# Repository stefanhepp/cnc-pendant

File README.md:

README
------

CNC Pendant for bCNC grbl controller.

License
-------
Shield: [![CC BY-SA 4.0][cc-by-sa-shield]][cc-by-sa]

This work is licensed under a
[Creative Commons Attribution-ShareAlike 4.0 International License][cc-by-sa].

[![CC BY-SA 4.0][cc-by-sa-image]][cc-by-sa]

[cc-by-sa]: http://creativecommons.org/licenses/by-sa/4.0/
[cc-by-sa-image]: https://licensebuttons.net/l/by-sa/4.0/88x31.png
[cc-by-sa-shield]: https://img.shields.io/badge/License-CC%20BY--SA%204.0-lightgrey.svg

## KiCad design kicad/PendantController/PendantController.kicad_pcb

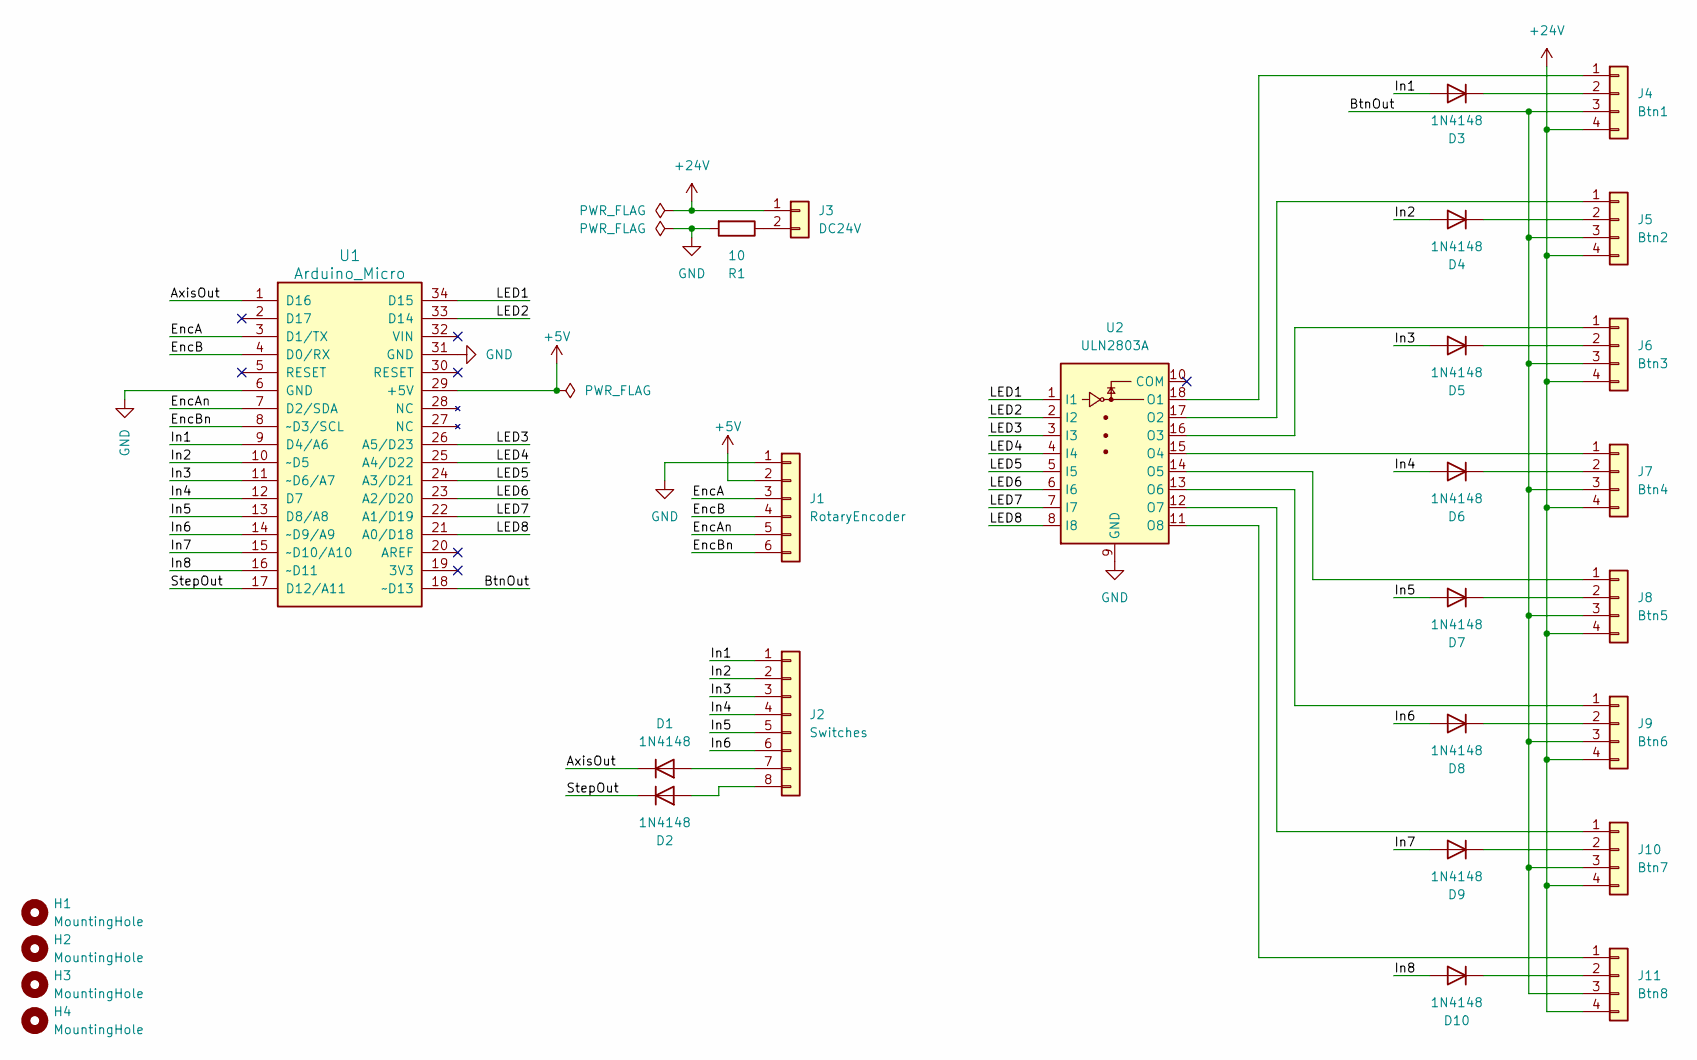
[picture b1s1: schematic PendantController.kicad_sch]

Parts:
D1, D2, D3, D4, D5, D6, D7, D8, D9, D10: 1N4148; D_DO-35_SOD27_P7.62mm_Horizontal
H1, H2, H3, H4: MountingHole; MountingHole_3.2mm_M3
J1: RotaryEncoder; PinHeader_1x06_P2.54mm_Vertical
J2: Switches; PinHeader_1x08_P2.54mm_Vertical
J3: DC24V; PinHeader_1x02_P2.54mm_Vertical
J4: Btn1; JST_XH_B4B-XH-A_1x04_P2.50mm_Vertical
J5: Btn2; JST_XH_B4B-XH-A_1x04_P2.50mm_Vertical
J6: Btn3; JST_XH_B4B-XH-A_1x04_P2.50mm_Vertical
J7: Btn4; JST_XH_B4B-XH-A_1x04_P2.50mm_Vertical
J8: Btn5; JST_XH_B4B-XH-A_1x04_P2.50mm_Vertical
J9: Btn6; JST_XH_B4B-XH-A_1x04_P2.50mm_Vertical
J10: Btn7; JST_XH_B4B-XH-A_1x04_P2.50mm_Vertical
J11: Btn8; JST_XH_B4B-XH-A_1x04_P2.50mm_Vertical
R1: 10; R_Axial_DIN0309_L9.0mm_D3.2mm_P12.70mm_Horizontal
U1: Arduino_Micro
U2: ULN2803A; DIP-18_W7.62mm

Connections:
+5V: J1.2, U1.29 (+5V)
+24V: J3.1, J4.4, J5.4, J6.4, J7.4, J8.4, J9.4, J10.4, J11.4
/AxisOut: D1.1 (K), U1.1 (D16)
/BtnOut: J4.3, J5.3, J6.3, J7.3, J8.3, J9.3, J10.3, J11.3, U1.18 (~D13)
/EncA: J1.3, U1.3 (D1/TX)
/EncAn: J1.5, U1.7 (D2/SDA)
/EncB: J1.4, U1.4 (D0/RX)
/EncBn: J1.6, U1.8 (~D3/SCL)
/In1: D3.2 (A), J2.1, U1.9 (D4/A6)
/In2: D4.2 (A), J2.2, U1.10 (~D5)
/In3: D5.2 (A), J2.3, U1.11 (~D6/A7)
/In4: D6.2 (A), J2.4, U1.12 (D7)
/In5: D7.2 (A), J2.5, U1.13 (D8/A8)
/In6: D8.2 (A), J2.6, U1.14 (~D9/A9)
/In7: D9.2 (A), U1.15 (~D10/A10)
/In8: D10.2 (A), U1.16 (~D11)
/LED1: U1.34 (D15), U2.1 (I1)
/LED2: U1.33 (D14), U2.2 (I2)
/LED3: U1.26 (A5/D23), U2.3 (I3)
/LED4: U1.25 (A4/D22), U2.4 (I4)
/LED5: U1.24 (A3/D21), U2.5 (I5)
/LED6: U1.23 (A2/D20), U2.6 (I6)
/LED7: U1.22 (A1/D19), U2.7 (I7)
/LED8: U1.21 (A0/D18), U2.8 (I8)
/StepOut: D2.1 (K), U1.17 (D12/A11)
GND: J1.1, R1.2, U1.6 (GND), U1.31 (GND), U2.9 (GND)
unnamed: D1.2 (A), J2.7
unnamed: D2.2 (A), J2.8
unnamed: D3.1 (K), J4.2
unnamed: D4.1 (K), J5.2
unnamed: D5.1 (K), J6.2
unnamed: D6.1 (K), J7.2
unnamed: D7.1 (K), J8.2
unnamed: D8.1 (K), J9.2
unnamed: D9.1 (K), J10.2
unnamed: D10.1 (K), J11.2
unnamed: J3.2, R1.1
unnamed: J4.1, U2.18 (O1)
unnamed: J5.1, U2.17 (O2)
unnamed: J6.1, U2.16 (O3)
unnamed: J7.1, U2.15 (O4)
unnamed: J8.1, U2.14 (O5)
unnamed: J9.1, U2.13 (O6)
unnamed: J10.1, U2.12 (O7)
unnamed: J11.1, U2.11 (O8)

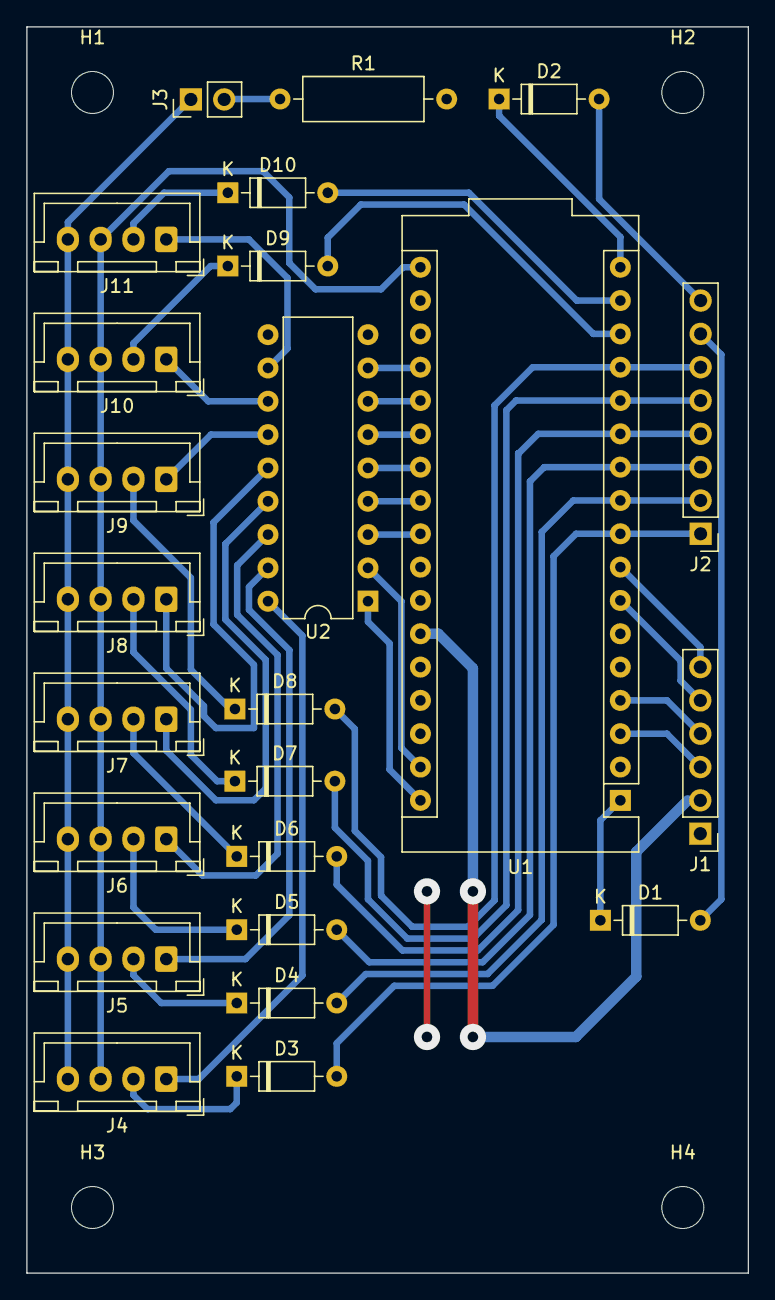
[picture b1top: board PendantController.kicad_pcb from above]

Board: 2 copper layers, 55.0 x 95.0 mm, 28 parts (0 on the bottom side), 45 nets.

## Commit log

2023-06-24 Updated case design with larger clearance, slimmer body.
2024-03-11 Wiring and initial schematics for IO Adapter
2024-03-12 Added IO breakout board PCB and case bottom cover
2024-03-13 Updated BOM export settings
2024-03-19 Added firmware platformio template
2024-03-24 Added case cover step file
2024-04-19 Export PCB to gerber settings
2024-05-05 Added cable plug adapter, use 0.4mm spacing for PCB
2024-05-12 Updated PCB layout
